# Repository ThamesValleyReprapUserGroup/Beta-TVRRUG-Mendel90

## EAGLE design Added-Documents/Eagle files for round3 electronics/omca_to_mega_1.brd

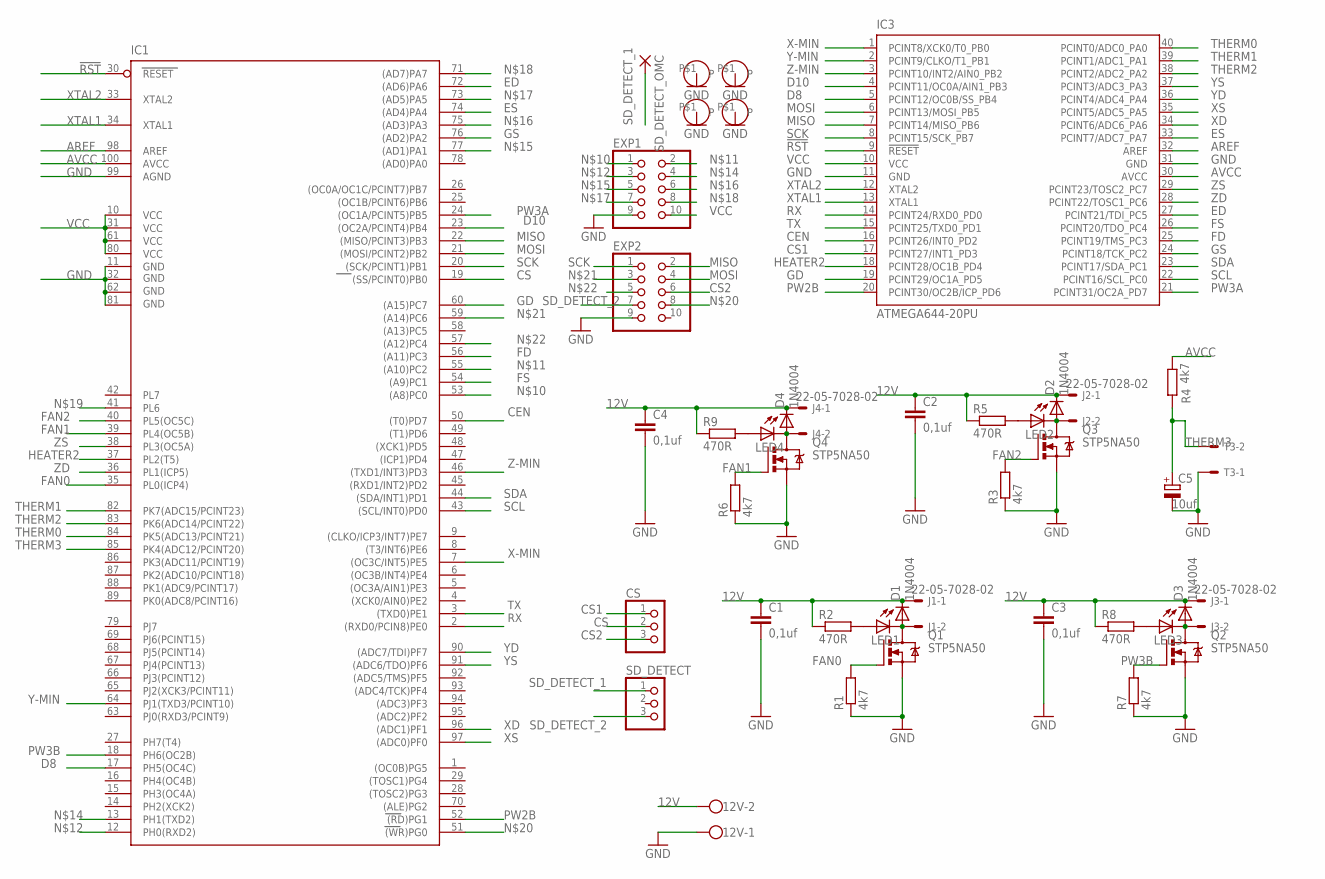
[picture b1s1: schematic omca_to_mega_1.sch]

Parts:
12V: W237-102
C1, C2, C3, C4: 0,1uf; C025-024X044; MPN K104K15X7RF53L2
C5: 10uf; TT2D4; MPN 100YXF10MEFC6.3X11
CS: PINHD-1X3; 1X03
D1, D2, D3, D4: 1N4004; D-7.5; MPN 1N4004RL
EXP1, EXP2: PINHD-2X5; 2X05
IC1: ATMEGA2560-16AU; TQFP100
IC3: ATMEGA644-20PU; DIL40; MPN ATMEGA644-20PU
J1, J2, J3, J4: 22-05-7028-02; 7395-02; MPN 22-05-7028
LED1, LED2, LED3, LED4: LED3MM; MPN L-93WEYW
Q1, Q2, Q3, Q4: STP5NA50; TO220BV; MPN STP55NF06L.
R1, R3, R6, R7: 4k7; 0204/7; MPN MFR4 10K 1%
R2, R5, R8, R9: 470R; 0204/7; MPN MFR4 470R 1%
R4: 4k7; 0204/7; MPN MFR4 4K7 1%
SD_DETECT: PINHD-1X3; 1X03
SD_DETECT_OMC: 1,6/0,8
T3: 22-05-7028-02; 7395-02; MPN 22-05-7028
U$2, U$3, U$4, U$5: HOLE

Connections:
12V: 12V.2, C1.1, C2.1, C3.1, C4.1, D1.C, D2.C, D3.C, D4.C, J1.1, J2.1, J3.1, J4.1, R2.1, R5.1, R8.1, R9.1
!RST: IC1.30 (RESET), IC3.9 (!RESET)
AREF: IC1.98 (AREF), IC3.32 (AREF)
AVCC: IC1.100 (AVCC), IC3.30 (AVCC), R4.1
CEN: IC1.50 ((T0)PD7), IC3.16 (PCINT26/INT0_PD2)
CS: CS.2, IC1.19 ((SS/PCINT0)PB0)
CS1: CS.1, IC3.17 (PCINT27/INT1_PD3)
CS2: CS.3, EXP2.6
D8: IC1.17 (PH5(OC4C)), IC3.5 (PCINT12/OC0B/SS_PB4)
D10: IC1.23 ((OC2A/PCINT4)PB4), IC3.4 (PCINT11/OC0A/AIN1_PB3)
ED: IC1.72 ((AD6)PA6), IC3.27 (PCINT21/TDI_PC5)
ES: IC1.74 ((AD4)PA4), IC3.33 (PCINT7/ADC7_PA7)
FAN0: IC1.35 (PL0(ICP4)), Q1.G, R1.2
FAN1: IC1.39 (PL4(OC5B)), Q4.G, R6.2
FAN2: IC1.40 (PL5(OC5C)), Q3.G, R3.2
FD: IC1.56 ((A11)PC3), IC3.25 (PCINT19/TMS_PC3)
FS: IC1.54 ((A9)PC1), IC3.26 (PCINT20/TDO_PC4)
GD: IC1.60 ((A15)PC7), IC3.19 (PCINT29/OC1A_PD5)
GND: 12V.1, C1.2, C2.2, C3.2, C4.2, C5.-, EXP1.9, EXP2.9, IC1.11 (GND), IC1.32 (GND1), IC1.62 (GND2), IC1.81 (GND3), IC1.99 (AGND), IC3.11 (GND), IC3.31 (GND), Q1.S, Q2.S, Q3.S, Q4.S, R1.1, R3.1, R6.1, R7.1, T3.1, U$2.P$1, U$3.P$1, U$4.P$1, U$5.P$1
GS: IC1.76 ((AD2)PA2), IC3.24 (PCINT18/TCK_PC2)
HEATER2: IC1.37 (PL2(T5)), IC3.18 (PCINT28/OC1B_PD4)
MISO: EXP2.2, IC1.22 ((MISO/PCINT3)PB3), IC3.7 (PCINT14/MISO_PB6)
MOSI: EXP2.4, IC1.21 ((MOSI/PCINT2)PB2), IC3.6 (PCINT13/MOSI_PB5)
unnamed: D1.A, J1.2, LED1.K (C), Q1.D
unnamed: LED1.A, R2.2
unnamed: D2.A, J2.2, LED2.K (C), Q3.D
unnamed: LED2.A, R5.2
unnamed: D4.A, J4.2, LED4.K (C), Q4.D
unnamed: LED4.A, R9.2
unnamed: EXP1.1, IC1.53 ((A8)PC0)
unnamed: EXP1.2, IC1.55 ((A10)PC2)
unnamed: EXP1.3, IC1.12 (PH0(RXD2))
unnamed: D3.A, J3.2, LED3.K (C), Q2.D
unnamed: EXP1.4, IC1.13 (PH1(TXD2))
unnamed: EXP1.5, IC1.77 ((AD1)PA1)
unnamed: EXP1.6, IC1.75 ((AD3)PA3)
unnamed: EXP1.7, IC1.73 ((AD5)PA5)
unnamed: EXP1.8, IC1.71 ((AD7)PA7)
unnamed: EXP2.8, IC1.51 ((WR)PG0)
unnamed: EXP2.3, IC1.59 ((A14)PC6)
unnamed: EXP2.5, IC1.57 ((A12)PC4)
unnamed: LED3.A, R8.2
PW2B: IC1.52 ((RD)PG1), IC3.20 (PCINT30/OC2B/ICP_PD6)
PW3A: IC1.24 ((OC1A/PCINT5)PB5), IC3.21 (PCINT31/OC2A_PD7)
PW3B: IC1.18 (PH6(OC2B)), Q2.G, R7.2
RX: IC1.2 ((RXD0/PCIN8)PE0), IC3.14 (PCINT24/RXD0_PD0)
SCK: EXP2.1, IC1.20 ((SCK/PCINT1)PB1), IC3.8 (PCINT15/SCK_PB7)
SCL: IC1.43 ((SCL/INT0)PD0), IC3.22 (PCINT16/SCL_PC0)
SDA: IC1.44 ((SDA/INT1)PD1), IC3.23 (PCINT17/SDA_PC1)
SD_DETECT_1: SD_DETECT.1, SD_DETECT_OMC.1
SD_DETECT_2: EXP2.7, SD_DETECT.3
THERM0: IC1.84 (PK5(ADC13/PCINT21)), IC3.40 (PCINT0/ADC0_PA0)
THERM1: IC1.82 (PK7(ADC15/PCINT23)), IC3.39 (PCINT1/ADC1_PA1)
THERM2: IC1.83 (PK6(ADC14/PCINT22)), IC3.38 (PCINT2/ADC2_PA2)
THERM3: C5.+, IC1.85 (PK4(ADC12/PCINT20)), R4.2, T3.2
TX: IC1.3 ((TXD0)PE1), IC3.15 (PCINT25/TXD0_PD1)
VCC: EXP1.10, IC1.10 (VCC), IC1.31 (VCC1), IC1.61 (VCC2), IC1.80 (VCC3), IC3.10 (VCC)
X-MIN: IC1.7 ((OC3C/INT5)PE5), IC3.1 (PCINT8/XCK0/T0_PB0)
XD: IC1.96 ((ADC1)PF1), IC3.34 (PCINT6/ADC6_PA6)
XS: IC1.97 ((ADC0)PF0), IC3.35 (PCINT5/ADC5_PA5)
XTAL1: IC1.34 (XTAL1), IC3.13 (XTAL1)
XTAL2: IC1.33 (XTAL2), IC3.12 (XTAL2)
Y-MIN: IC1.64 (PJ1(TXD3/PCINT10)), IC3.2 (PCINT9/CLKO/T1_PB1)
YD: IC1.90 ((ADC7/TDI)PF7), IC3.36 (PCINT4/ADC4_PA4)
YS: IC1.91 ((ADC6/TDO)PF6), IC3.37 (PCINT3/ADC3_PA3)
Z-MIN: IC1.46 ((TXD1/INT3)PD3), IC3.3 (PCINT10/INT2/AIN0_PB2)
ZD: IC1.36 (PL1(ICP5)), IC3.28 (PCINT22/TOSC1_PC6)
ZS: IC1.38 (PL3(OC5A)), IC3.29 (PCINT23/TOSC2_PC7)

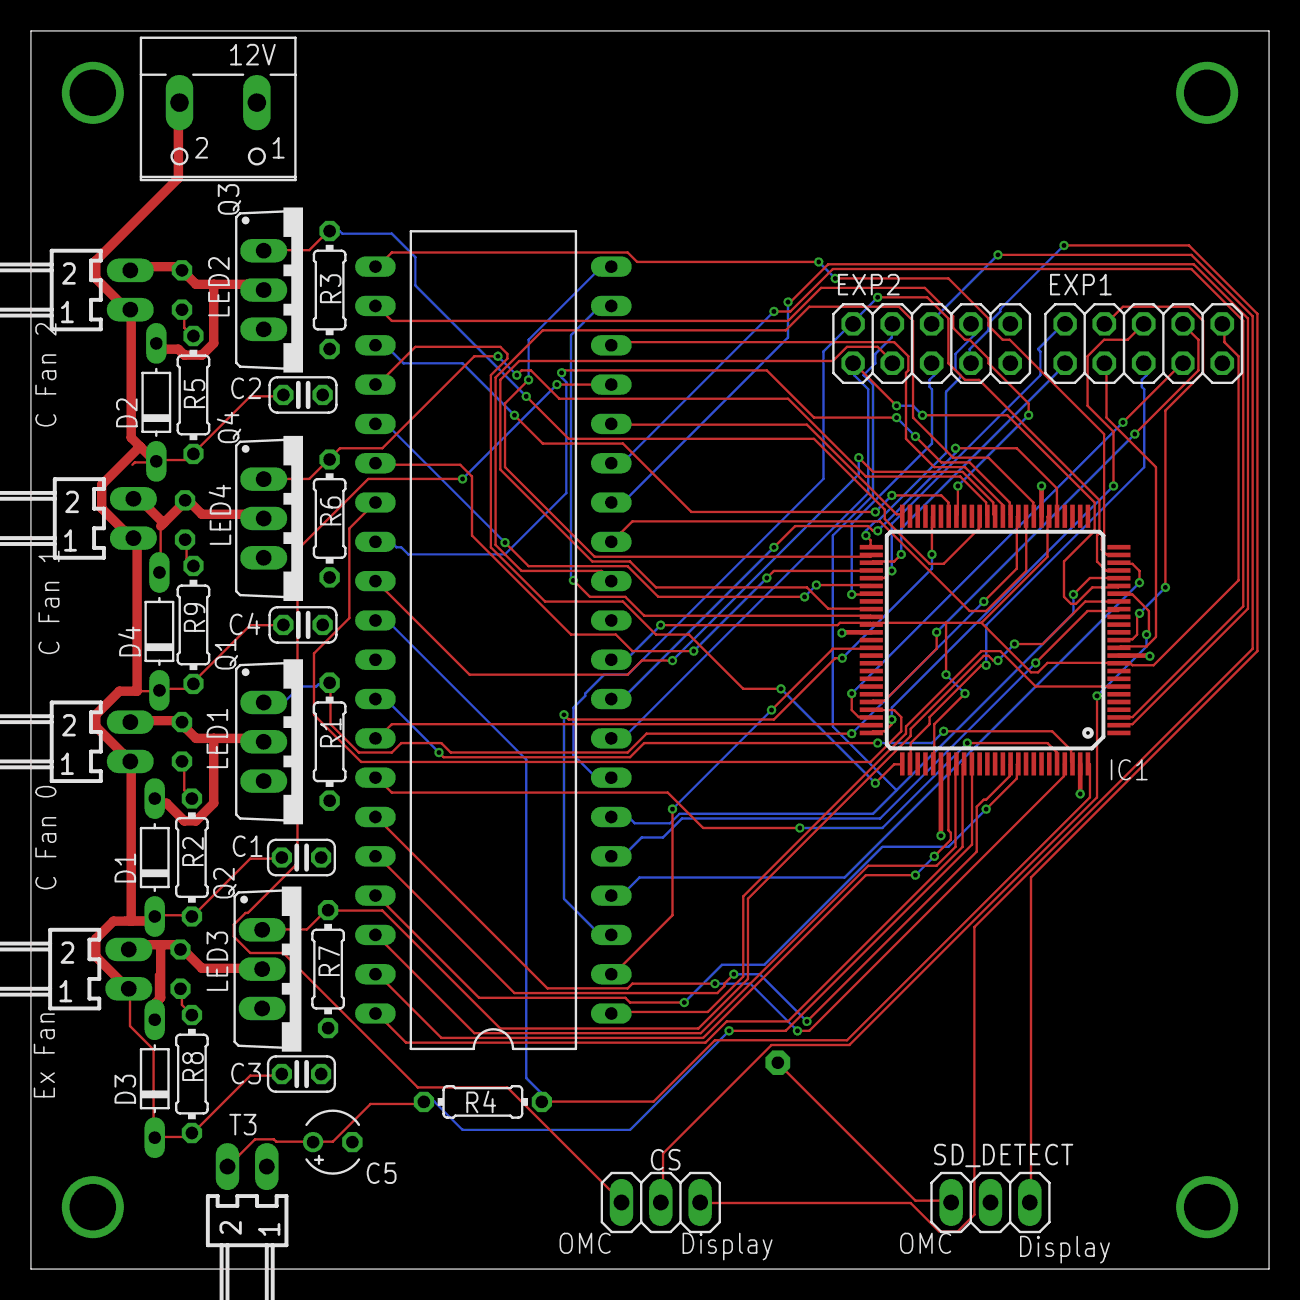
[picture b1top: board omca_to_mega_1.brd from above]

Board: 2 copper layers, 80.0 x 80.0 mm, 43 parts (0 on the bottom side), 68 nets.

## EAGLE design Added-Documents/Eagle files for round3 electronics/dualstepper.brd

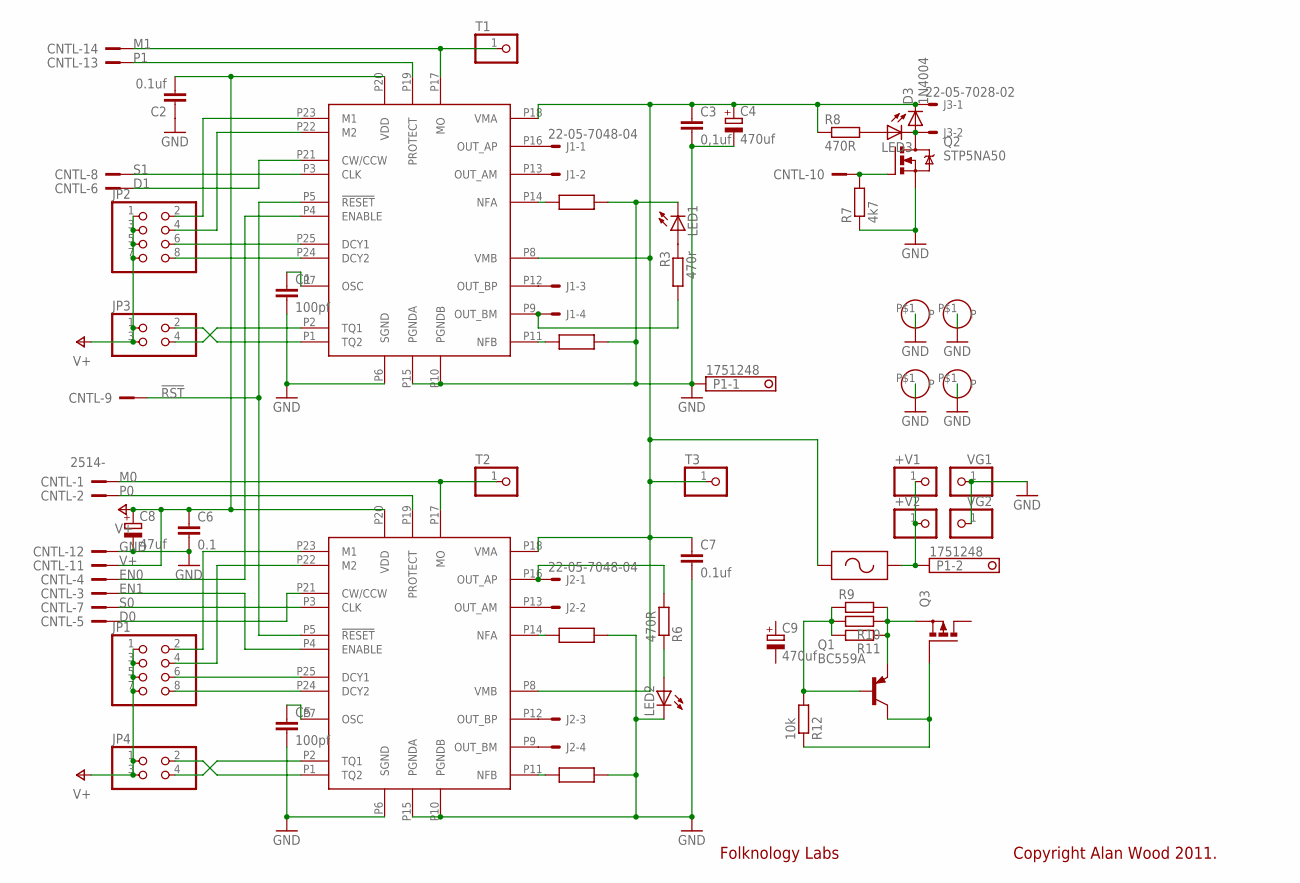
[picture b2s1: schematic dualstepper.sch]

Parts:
+V1, +V2: PINHD-1X1; 1X01; MPN 90120-0761
C1, C5: 100pf; C025-024X044; MPN SR151A101JAR
C2, C7: 0.1uf; C025-024X044; MPN K104K15X7RF53L2
C3: 0,1uf; C025-024X044; MPN K104K15X7RF53L2
C4: 470uf; E22-9; MPN MCTEA471M1EB-1021P
C6: 0.1; C025-024X044; MPN K104K15X7RF53L2
C8: 47uf; E1,8-4; MPN 16YXF47MEFC5X11
C9: 470uf; E3,5-8; MPN MCTEA471M1EB-1021P
CNTL: 2514-; PAK100/2500-14; MPN 09 18 510 7323
D3: 1N4004; D-7.5; MPN 1N4004RL
J1, J2: 22-05-7048-04; 7395-04; MPN 22-05-7048
J3: 22-05-7028-02; 7395-02; MPN 22-05-7028
JP1, JP2: PINHD-2X4; 2X04; MPN M20-9980446
JP3, JP4: PINHD-2X2; 2X02; MPN TSW-101-07-T-D
LED1, LED2, LED3: LED3MM; MPN L-93WEYW
P1: 1751248; MPN CTB3051/2
Q1: BC559A; TO92-EBC
Q2: STP5NA50; TO220BV; MPN STP55NF06L.
Q3: PMOSFET_PTO220BV; TO220BV
R1, R2, R4, R5: R22; R20; MPN WP4S-R22JA2
R3: 470r; 0204/7; MPN MFR4 470R 1%
R6, R8: 470R; 0204/7; MPN MFR4 470R 1%
R7: 4k7; 0204/7; MPN MFR4 10K 1%
R9, R10, R11: R-EU_0411/3V; 0411V
R12: 10k; 0204/7; MPN MFR4 470R 1%
T1, T2, T3: PINHD-1X1; 1X01; MPN 90120-0761
U$1, U$2: TB6560AHQ; HZIP25-P-1.27
U$3, U$4, U$5, U$6: HOLE
U$7: RXEFXXX-RAYCHEM-POLYSWITCH10.2; 2*10.2; MPN AGRF1000
VG1, VG2: PINHD-1X1; 1X01; MPN 90120-0761

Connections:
!RST: CNTL.9, U$1.P5 (!RESET), U$2.P5 (!RESET)
D0: CNTL.5, U$1.P21 (CW/CCW)
D1: CNTL.6, U$2.P21 (CW/CCW)
EN0: CNTL.4, U$2.P4 (ENABLE)
EN1: CNTL.3, U$1.P4 (ENABLE)
GND: C1.2, C2.1, C3.2, C4.-, C5.2, C6.2, C7.2, C8.-, CNTL.12, LED1.K (C), LED2.K (C), P1.1, Q2.S, R1.P$2 (2), R2.P$2 (2), R4.P$2 (2), R5.P$2 (2), R7.1, U$1.P6 (SGND), U$1.P10 (PGNDB), U$1.P15 (PGNDA), U$2.P6 (SGND), U$2.P10 (PGNDB), U$2.P15 (PGNDA), U$3.P$1, U$4.P$1, U$5.P$1, U$6.P$1, VG1.1, VG2.1
M0: CNTL.1, T2.1, U$1.P17 (MO)
M1: CNTL.14, T1.1, U$2.P17 (MO)
unnamed: +V1.1, +V2.1, P1.2, U$7.P$2
unnamed: J1.2, U$2.P13 (OUT_AM)
unnamed: J1.3, U$2.P12 (OUT_BP)
unnamed: J1.4, R3.2, U$2.P9 (OUT_BM)
unnamed: C1.1, U$2.P7 (OSC)
unnamed: JP2.2, U$2.P23 (M1)
unnamed: J2.2, U$1.P13 (OUT_AM)
unnamed: LED2.A, R6.1
unnamed: LED1.A, R3.1
unnamed: J2.3, U$1.P12 (OUT_BP)
unnamed: JP3.2, U$2.P1 (TQ2)
unnamed: JP3.4, U$2.P2 (TQ1)
unnamed: D3.A, J3.2, LED3.K (C), Q2.D
unnamed: J2.4, U$1.P9 (OUT_BM)
unnamed: J1.1, U$2.P16 (OUT_AP)
unnamed: Q1.B, R9.1, R10.2, R11.2, R12.2
unnamed: JP2.8, U$2.P24 (DCY2)
unnamed: JP2.6, U$2.P25 (DCY1)
unnamed: JP2.4, U$2.P22 (M2)
unnamed: Q1.E, Q3.S, R9.2, R10.1, R11.1
unnamed: J2.1, R6.2, U$1.P16 (OUT_AP)
unnamed: Q1.C, Q3.G, R12.1
unnamed: JP4.4, U$1.P2 (TQ1)
unnamed: JP4.2, U$1.P1 (TQ2)
unnamed: JP1.8, U$1.P24 (DCY2)
unnamed: JP1.6, U$1.P25 (DCY1)
unnamed: R2.P$1 (1), U$2.P11 (NFB)
unnamed: JP1.4, U$1.P22 (M2)
unnamed: R1.P$1 (1), U$2.P14 (NFA)
unnamed: R5.P$1 (1), U$1.P11 (NFB)
unnamed: R4.P$1 (1), U$1.P14 (NFA)
unnamed: C5.1, U$1.P7 (OSC)
unnamed: JP1.2, U$1.P23 (M1)
unnamed: CNTL.10, Q2.G, R7.2
unnamed: LED3.A, R8.2
P0: CNTL.2, U$1.P19 (PROTECT)
P1: CNTL.13, U$2.P19 (PROTECT)
S0: CNTL.7, U$1.P3 (CLK)
S1: CNTL.8, U$2.P3 (CLK)
V+: C2.2, C6.1, C8.+, CNTL.11, JP1.1, JP1.3, JP1.5, JP1.7, JP2.1, JP2.3, JP2.5, JP2.7, JP3.1, JP3.3, JP4.1, JP4.3, U$1.P20 (VDD), U$2.P20 (VDD)
VM: C3.1, C4.+, C7.1, D3.C, J3.1, R8.1, T3.1, U$1.P8 (VMB), U$1.P18 (VMA), U$2.P8 (VMB), U$2.P18 (VMA), U$7.P$1

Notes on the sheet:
Copyright Alan Wood 2011.
Folknology Labs

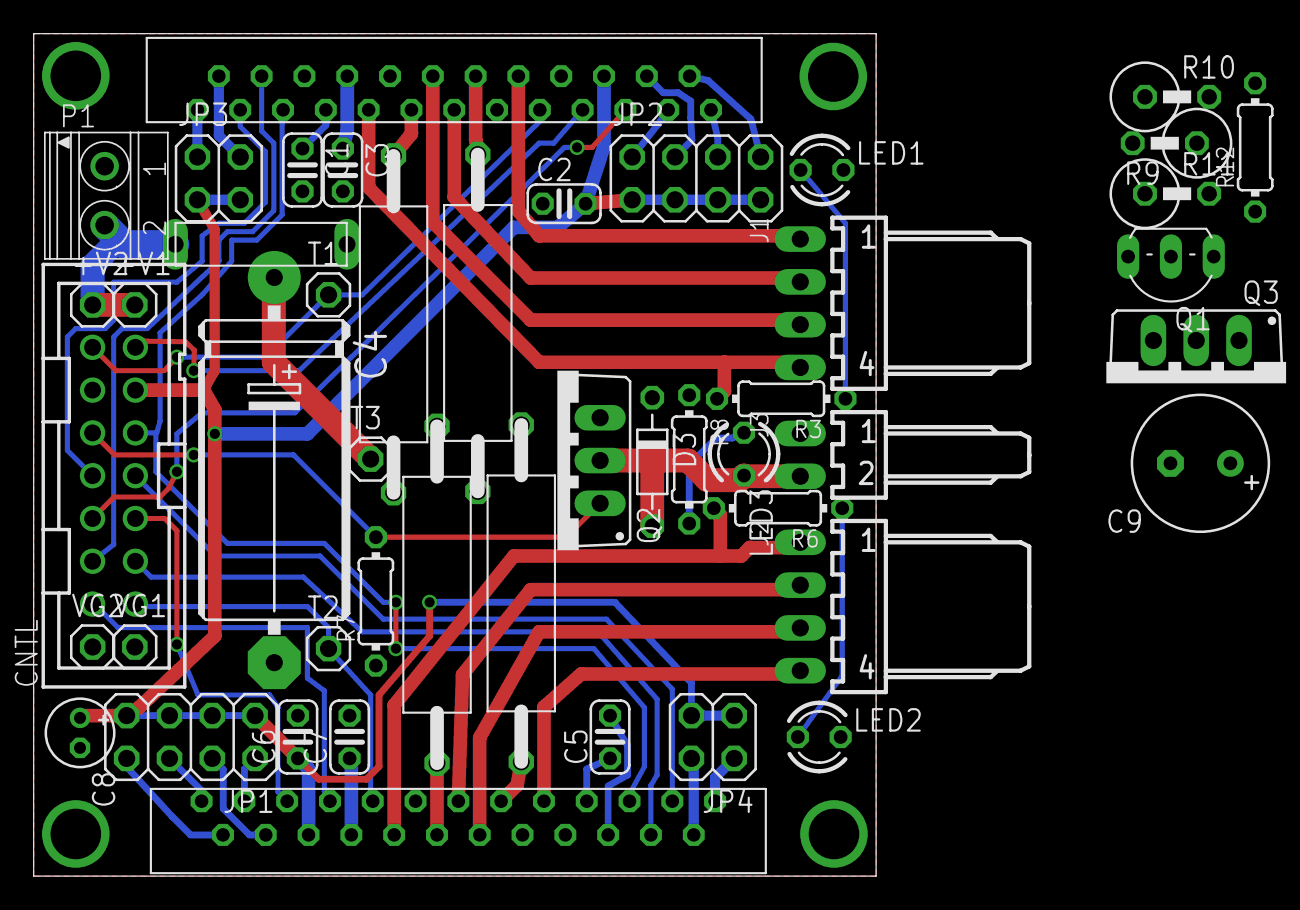
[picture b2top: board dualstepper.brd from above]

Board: 2 copper layers, 50.0 x 50.0 mm, 51 parts (0 on the bottom side), 49 nets.

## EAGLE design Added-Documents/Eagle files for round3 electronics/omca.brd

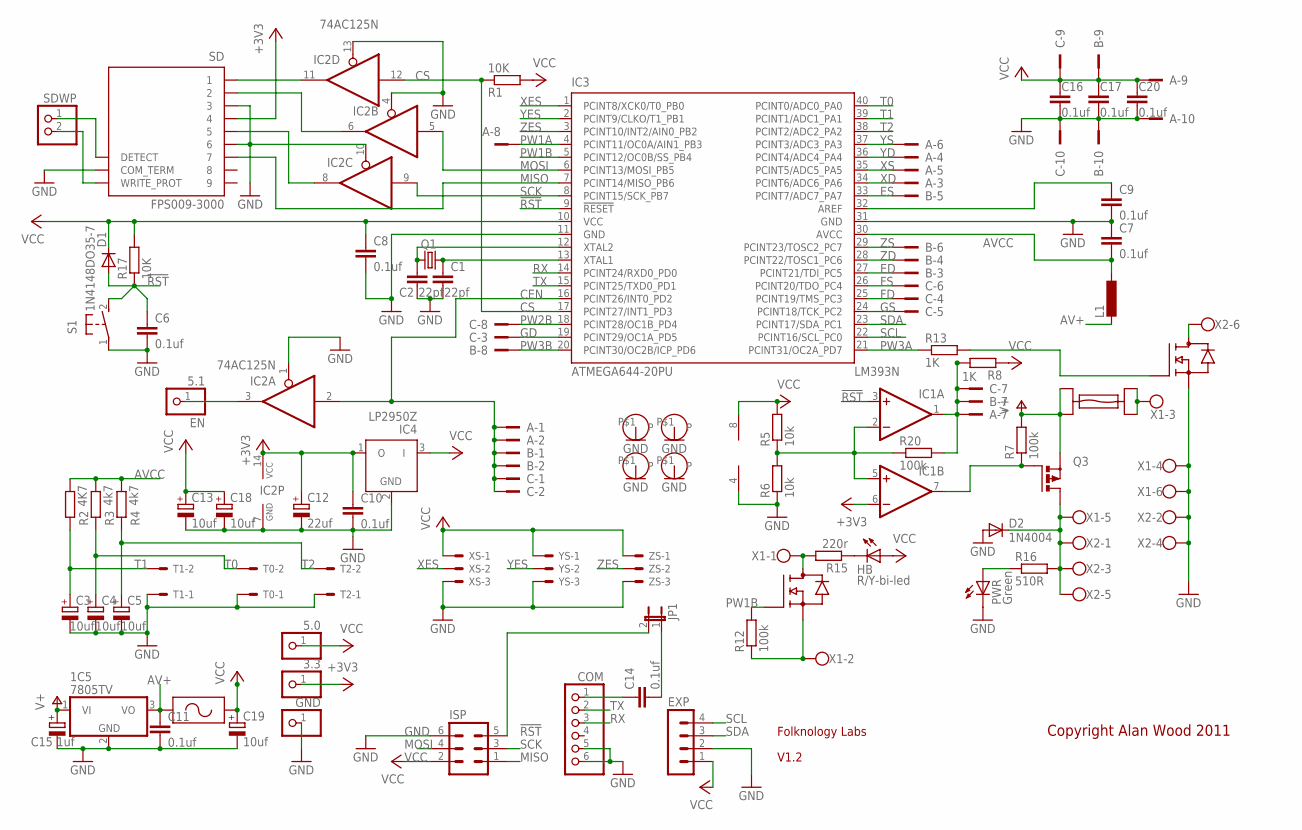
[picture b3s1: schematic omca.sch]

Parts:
1C5: 7805TV; TO220V; MPN L7805CV
3.3, 5.0: PINHD-1X1; 1X01; MPN 2211S-02G
5.1: EN; 1X01; MPN 2211S-02G
A: 2510-5; PAK100/2500-5-10; MPN 09 18 510 7323
B: 2510-5; PAK100/2500-5-10; MPN 09 18 510 7323
C: 2510-5; PAK100/2500-5-10; MPN 09 18 510 7323
C1, C2: 22pf; C025-024X044; MPN SR151A220JAR
C3, C4, C5: 10uf; TT2D4; MPN 100YXF10MEFC6.3X11
C6, C7, C8, C9, C10, C11, C14, C16, C17, C20: 0.1uf; C025-024X044; MPN K104K15X7RF53L2
C12: 22uf; TT2D5; MPN 100YXF10MEFC6.3X11
C13: 10uf; E2,5-6E; MPN 25ZL47MEFC5X11
C15: 1uf; E2-4; MPN 100YXF10MEFC6.3X11
C18, C19: 10uf; E2,5-6E; MPN 100YXF10MEFC6.3X11
COM: PINHD-1X6/90; 1X06/90; MPN MC34751
D1: 1N4148DO35-7; DO35-7; MPN 1N4148-TR
D2: 1N4004; DO41-10
EXP: MA04-1; MPN 826926-4
F1: MINIBLADEFUSEHOLDER; MINIFUSEHOLDER
F2: RXEFXXX-RAYCHEM-POLYSWITCH; 2*5.1
GND: PINHD-1X1; 1X01; MPN 2211S-02G
HB: R/Y-bi-led; LED3MM
IC1: LM393N; DIL08; MPN LM393NG
IC2: 74AC125N; DIL14; MPN SN74AHC125N
IC3: ATMEGA644-20PU; DIL40; MPN ATMEGA644-20PU
IC4: LP2950Z; TO92; MPN LP2950CZ-3.3/NOPB
ISP: ML6; MPN 09 18 506 7324
JP1: JP1E; JP1; MPN 2211S-02G
L1: L-EU0207/10; 0207/10; MPN MCAL0410A1-101KU
PWR: Green; LED3MM
Q1: CRYSTALHC49S; HC49/S; MPN HC49SM-3.6864-30-50-60-16-ATF
Q2: IPI80N03S4L-04TO262; TO262
Q3: PMOSFET_PTO220BV; TO220BV; MPN SUP75P03-07-E3
Q4: NTD4963N; IPAK
R1, R17: 10K; 0204/7; MPN MFR4 10K 1%
R2: 4K7; 0204/7; MPN MFR4 4K7 1%
R3, R4: 4k7; 0204/7; MPN MFR4 4K7 1%
R5, R6: 10k; 0204/7; MPN MFR4 10K 1%
R7, R12, R20: 100k; 0204/7; MPN MFR4 100K 1%
R8, R13: 1K; 0204/7; MPN MFR4 1K 1%
R15: 220r; 0204/7; MPN MFR4 470R 1%
R16: 510R; 0204/7; MPN MFR4 470R 1%
S1: 31-XX; B3F-31XX
SD: FPS009-3000; MPN SDAMB-01215BT00
SDWP: PINHD-1X2; 1X02; MPN 2211S-02G
T0, T1, T2: 22-05-7028-02; 7395-02; MPN 22-05-7028
U$2, U$3, U$4, U$5: HOLE
X1, X2: W237-6
XS: 22-05-7038-03; 7395-03; MPN 22-05-7038
YS: 22-05-7038-03; 7395-03; MPN 22-05-7038
ZS: 22-05-7038-03; 7395-03; MPN 22-05-7038

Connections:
!RST: C6.1, D1.A, IC1.3 (+IN), IC3.9 (!RESET), ISP.5, JP1.2, R17.1, S1.2 (S)
!SRST: A.7, B.7, C.7, IC1.1 (OUT), R8.2, R20.2
+3V3: 3.3.1, C10.1, C12.+, IC1.6 (-IN), IC2.14 (VCC), IC4.1 (O), SD.4
AV+: 1C5.3 (VO), C11.1, F2.P$1, L1.2
AVCC: C7.2, IC3.30 (AVCC), L1.1, R2.1, R3.1, R4.1
CEN: A.1, A.2, B.1, B.2, C.1, C.2, IC2.2 (I), IC3.16 (PCINT26/INT0_PD2)
CS: IC2.12 (I), IC3.17 (PCINT27/INT1_PD3), R1.1
ED: B.3, IC3.27 (PCINT21/TDI_PC5)
ES: B.5, IC3.33 (PCINT7/ADC7_PA7)
FD: C.4, IC3.25 (PCINT19/TMS_PC3)
FS: C.6, IC3.26 (PCINT20/TDO_PC4)
GD: C.3, IC3.19 (PCINT29/OC1A_PD5)
GND: 1C5.2 (GND), A.10, B.10, C.10, C1.2, C2.2, C3.-, C4.-, C5.-, C6.2, C7.1, C8.2, C9.2, C10.2, C11.2, C12.-, C13.-, C15.-, C16.2, C17.2, C18.-, C19.-, C20.2, COM.5, COM.6, D2.A, EXP.2, GND.1, IC1.4 (V-), IC2.1 (OE), IC2.4 (OE), IC2.7 (GND), IC2.10 (OE), IC2.13 (OE), IC3.11 (GND), IC3.31 (GND), IC4.2 (GND), ISP.6, PWR.K (C), Q4.P$3 (S), R6.1, S1.1, SD.3, SD.6, SD.COM_TERM, T0.1, T1.1, T2.1, U$2.P$1, U$3.P$1, U$4.P$1, U$5.P$1, X1.4, X1.6, X2.2, X2.4, XS.3, YS.3, ZS.3
GS: C.5, IC3.24 (PCINT18/TCK_PC2)
MISO: IC3.7 (PCINT14/MISO_PB6), ISP.1, SD.7
MOSI: IC2.5 (I), IC3.6 (PCINT13/MOSI_PB5), ISP.4
unnamed: IC2.11 (O), SD.1
unnamed: IC2.6 (O), SD.2
unnamed: IC2.8 (O), SD.5
unnamed: HB.K (C), R15.1
unnamed: C14.1, COM.1
unnamed: SD.WRITE_PROT, SDWP.2
unnamed: 5.1.1, IC2.3 (O)
unnamed: Q2.2 (D), R15.2, X1.1
unnamed: Q2.3 (S), R12.1, X1.2
unnamed: Q4.P$2 (D), X2.6
unnamed: IC1.2 (-IN), IC1.5 (+IN), R5.1, R6.2, R20.1
unnamed: SD.DETECT, SDWP.1
unnamed: IC1.7 (OUT), Q3.G, R7.1
unnamed: Q4.P$1 (G), R13.2
unnamed: D2.C, Q3.D, R16.2, X1.5, X2.1, X2.3, X2.5
unnamed: PWR.A, R16.1
unnamed: F1.P$1 (F1A), F1.P$2 (F1B), X1.3
unnamed: C14.2, JP1.1
unnamed: C2.1, IC3.12 (XTAL2), Q1.2
unnamed: C1.1, IC3.13 (XTAL1), Q1.1
unnamed: C9.1, IC3.32 (AREF)
PW1A: A.8, IC3.4 (PCINT11/OC0A/AIN1_PB3)
PW1B: IC3.5 (PCINT12/OC0B/SS_PB4), Q2.1 (G), R12.2
PW2B: C.8, IC3.18 (PCINT28/OC1B_PD4)
PW3A: IC3.21 (PCINT31/OC2A_PD7), R13.1
PW3B: B.8, IC3.20 (PCINT30/OC2B/ICP_PD6)
RX: COM.3, IC3.14 (PCINT24/RXD0_PD0)
SCK: IC2.9 (I), IC3.8 (PCINT15/SCK_PB7), ISP.3
SCL: EXP.4, IC3.22 (PCINT16/SCL_PC0)
SDA: EXP.3, IC3.23 (PCINT17/SDA_PC1)
T0: C4.+, IC3.40 (PCINT0/ADC0_PA0), R3.2, T0.2
T1: C3.+, IC3.39 (PCINT1/ADC1_PA1), R2.2, T1.2
T2: C5.+, IC3.38 (PCINT2/ADC2_PA2), R4.2, T2.2
TX: COM.2, IC3.15 (PCINT25/TXD0_PD1)
V+: 1C5.1 (VI), C15.+, F1.P$3 (F2A), F1.P$4 (F2B), Q3.S, R7.2
VCC: 5.0.1, A.9, B.9, C.9, C8.1, C13.+, C16.1, C17.1, C18.+, C19.+, C20.1, D1.C, EXP.1, F2.P$2, HB.A, IC1.8 (V+), IC3.10 (VCC), IC4.3 (I), ISP.2, R1.2, R5.2, R8.1, R17.2, XS.1, YS.1, ZS.1
XD: A.3, IC3.34 (PCINT6/ADC6_PA6)
XES: IC3.1 (PCINT8/XCK0/T0_PB0), XS.2
XS: A.5, IC3.35 (PCINT5/ADC5_PA5)
YD: A.4, IC3.36 (PCINT4/ADC4_PA4)
YES: IC3.2 (PCINT9/CLKO/T1_PB1), YS.2
YS: A.6, IC3.37 (PCINT3/ADC3_PA3)
ZD: B.4, IC3.28 (PCINT22/TOSC1_PC6)
ZES: IC3.3 (PCINT10/INT2/AIN0_PB2), ZS.2
ZS: B.6, IC3.29 (PCINT23/TOSC2_PC7)

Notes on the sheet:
Copyright Alan Wood 2011
Folknology Labs
V1.2

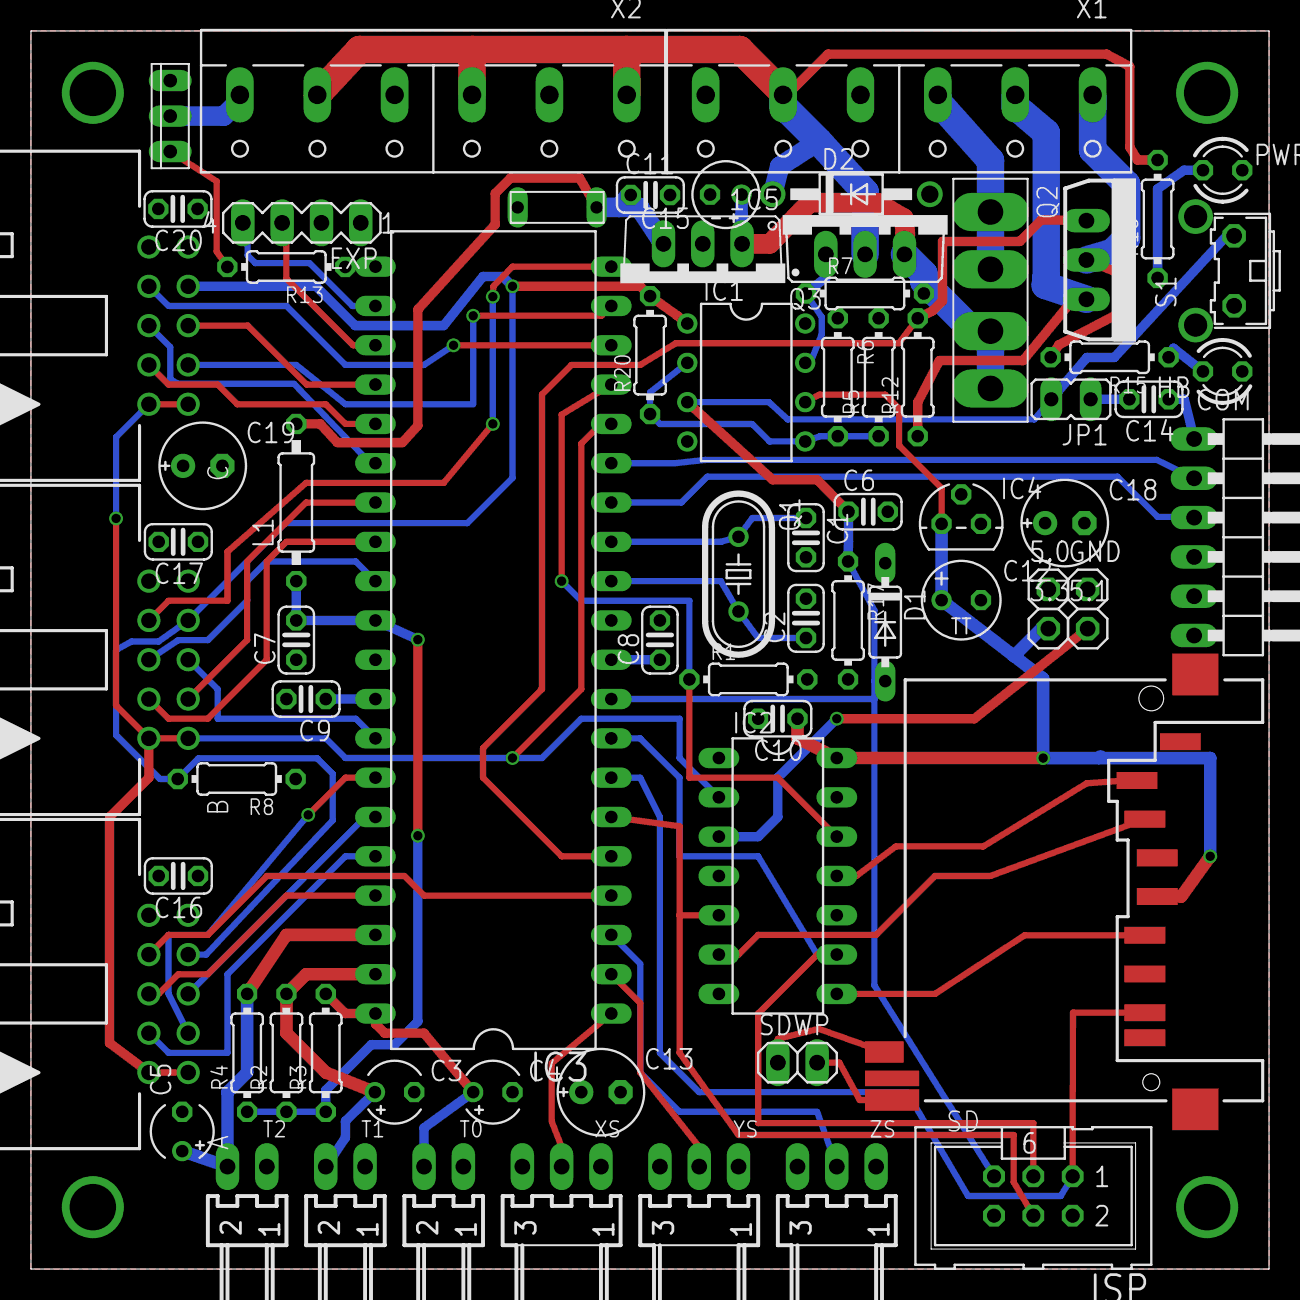
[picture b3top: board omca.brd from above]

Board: 2 copper layers, 80.0 x 80.0 mm, 76 parts (0 on the bottom side), 61 nets.

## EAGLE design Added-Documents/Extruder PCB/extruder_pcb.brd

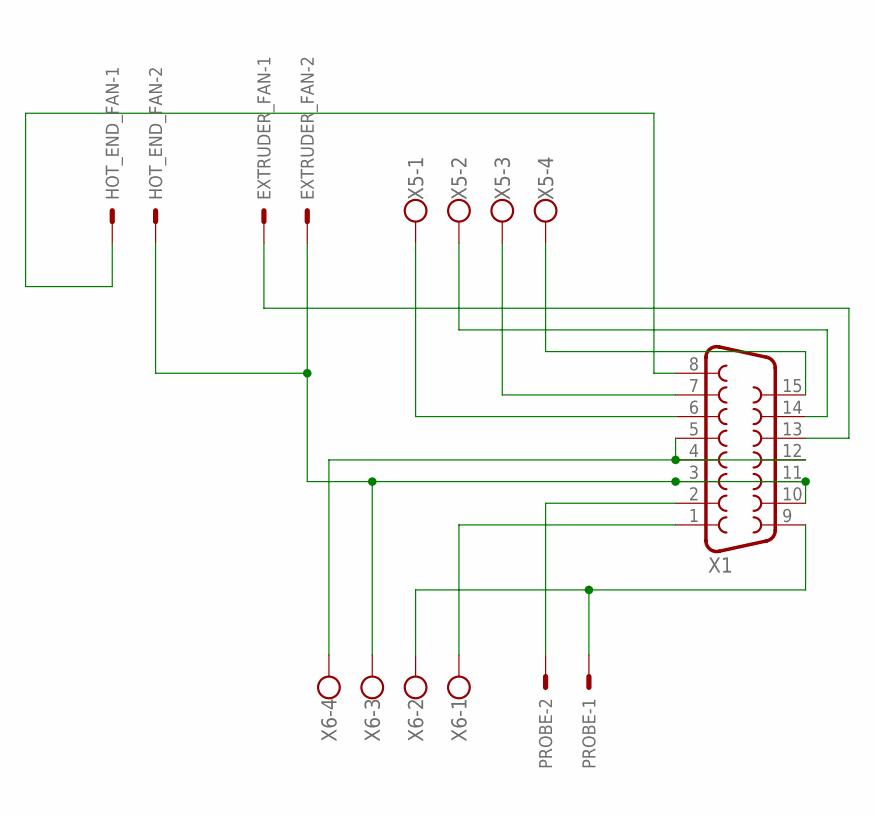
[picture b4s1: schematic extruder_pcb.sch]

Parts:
EXTRUDER_FAN: KK-156-2
HOT_END_FAN: KK-156-2
PROBE: KK-156-2
X1: F15VB
X5, X6: W237-4

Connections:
unnamed: X1.1, X6.1
unnamed: PROBE.2, X1.2
unnamed: EXTRUDER_FAN.2, HOT_END_FAN.2, X1.3, X1.10, X1.11, X6.3
unnamed: X1.4, X1.5, X1.12, X6.4
unnamed: PROBE.1, X1.9, X6.2
unnamed: EXTRUDER_FAN.1, X1.13
unnamed: X1.6, X5.1
unnamed: X1.14, X5.2
unnamed: X1.7, X5.3
unnamed: X1.15, X5.4
unnamed: HOT_END_FAN.1, X1.8

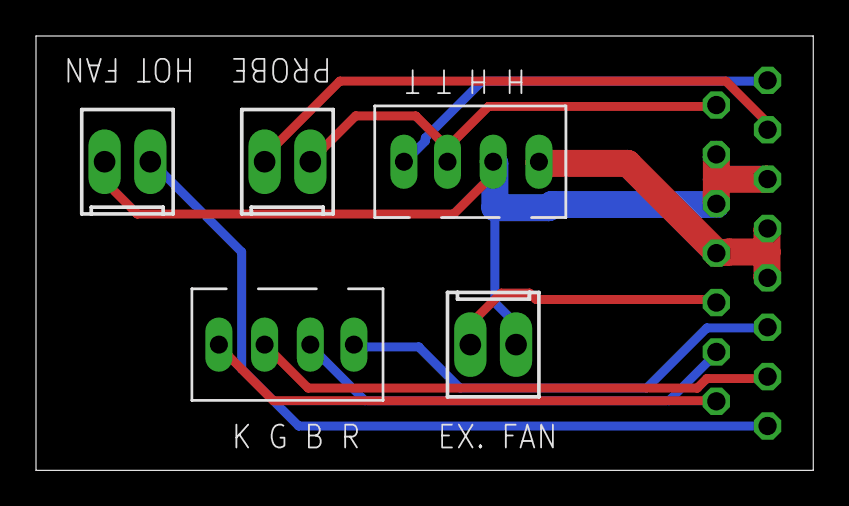
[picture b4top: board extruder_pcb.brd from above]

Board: 2 copper layers, 43.2 x 24.1 mm, 6 parts (1 on the bottom side), 11 nets.

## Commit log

2016-04-19 First run of script
    Had to start over. Lucky we don't need the changes I made first time
    arround - bh
2016-04-19 Sheets modded as agreed
2016-04-19 Added round3 electronics eagle files
    good for messurements etc
2016-04-20 Suggestion for Right hand side upgraders
2016-04-25 added zip tie to base
    by mistake it was deleted
2016-04-25 forgot to delete mouse hole
    even the best can have a bad eye :-D
2016-04-25 stays rotated...
    just mroe easy to look at and compare with gantry
2016-04-25 added enclousure plates
    to be considered experimental and not a part of the beta build
2016-04-25 heat shield
    For those that wants it. 1 is for the bottom one. 3 is for the top one
    as it has room for thermistor wire
2016-04-25 sheets corrected
    base was 4mm wider than svg... so made 4mm smaller. Gantry adjusted the
    same
2016-04-25 suggestin for alternative right stay
2016-04-25 R15 Versions of sheets
2016-04-25 put slot in alternative right stay
    having electronics on either side of the stay seems the only way. Again
    this is just a suggestion that looks very plaussible
2016-04-25 Enclosure back saved as R15
2016-04-25 Moved Enclosure in to subfolders
2016-04-26 very minor errors
    found some very minor errors we might want to fix once matt can confirm
    them
2016-04-26 renamed to md
2016-04-27 Json file for IDE 1.6.x
    allows IDE 1.6.x to automatic load hardware files
2016-04-27 hardware files for OMC
2016-04-27 corrected path to hardware zip
2016-04-27 wrong path before
2016-04-27 finish up json
2016-04-27 corrected checksum
2016-04-27 corrected size
2016-04-27 new checksum & size
2016-04-27 new board file... wrong structure on old one
2016-04-27 removed dual // in site link
2016-04-27 Added files via upload
2016-04-28 new checksum
2016-04-28 Rename How to add OMC to IDE 1.6.8.dk to How to add OMC to ID 1.6.8.MD
2016-04-28 enclosure with true circles
2016-04-28 updated enclosure sheets and saved as R15
2016-04-28 added marlin
    config is set to OMC... but nothing else changed.
2016-04-28 Rename How to add OMC to ID 1.6.8.MD to How to add OMC to ID 1.6.8.md
2016-05-21 daughter board
    makes omc look like ramps. support for 3 extruders and also cold end
    fans. on top full graphic display also.
2016-05-21 mighty core
    Adds support for not only 644p but also 1284p, with options to select
    run speed and burn bootloader direct from ide
2016-05-22 fatter tracks at fet's
2016-05-22 removed a few temp files
2016-05-22 added 2560 daughter board to marlin
2016-06-14 not needed anymore
    since builders will order themselves we dont need it
2016-06-14 endcap for the LED PSU
    matching switch is in the BOM
2016-06-14 added $fn=360; to the end cap
    Makes everything smooth round
2016-06-14 removed 2560 daughter board
    might be readded under different folder
2016-06-14 general cleanup and relocation
    marlin removed at it will not fit the OMC yet. They are also doing a
    bigger code cleanup at marlin so makes no sense to have it. Better would
    also be to fork it in to a seperate repro
2017-04-21 added 644p
2017-04-27 updated board def

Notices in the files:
Added-Documents/Eagle files for round3 electronics/dualstepper.sch:
LICENCE: Copyright Alan Wood 2011.
